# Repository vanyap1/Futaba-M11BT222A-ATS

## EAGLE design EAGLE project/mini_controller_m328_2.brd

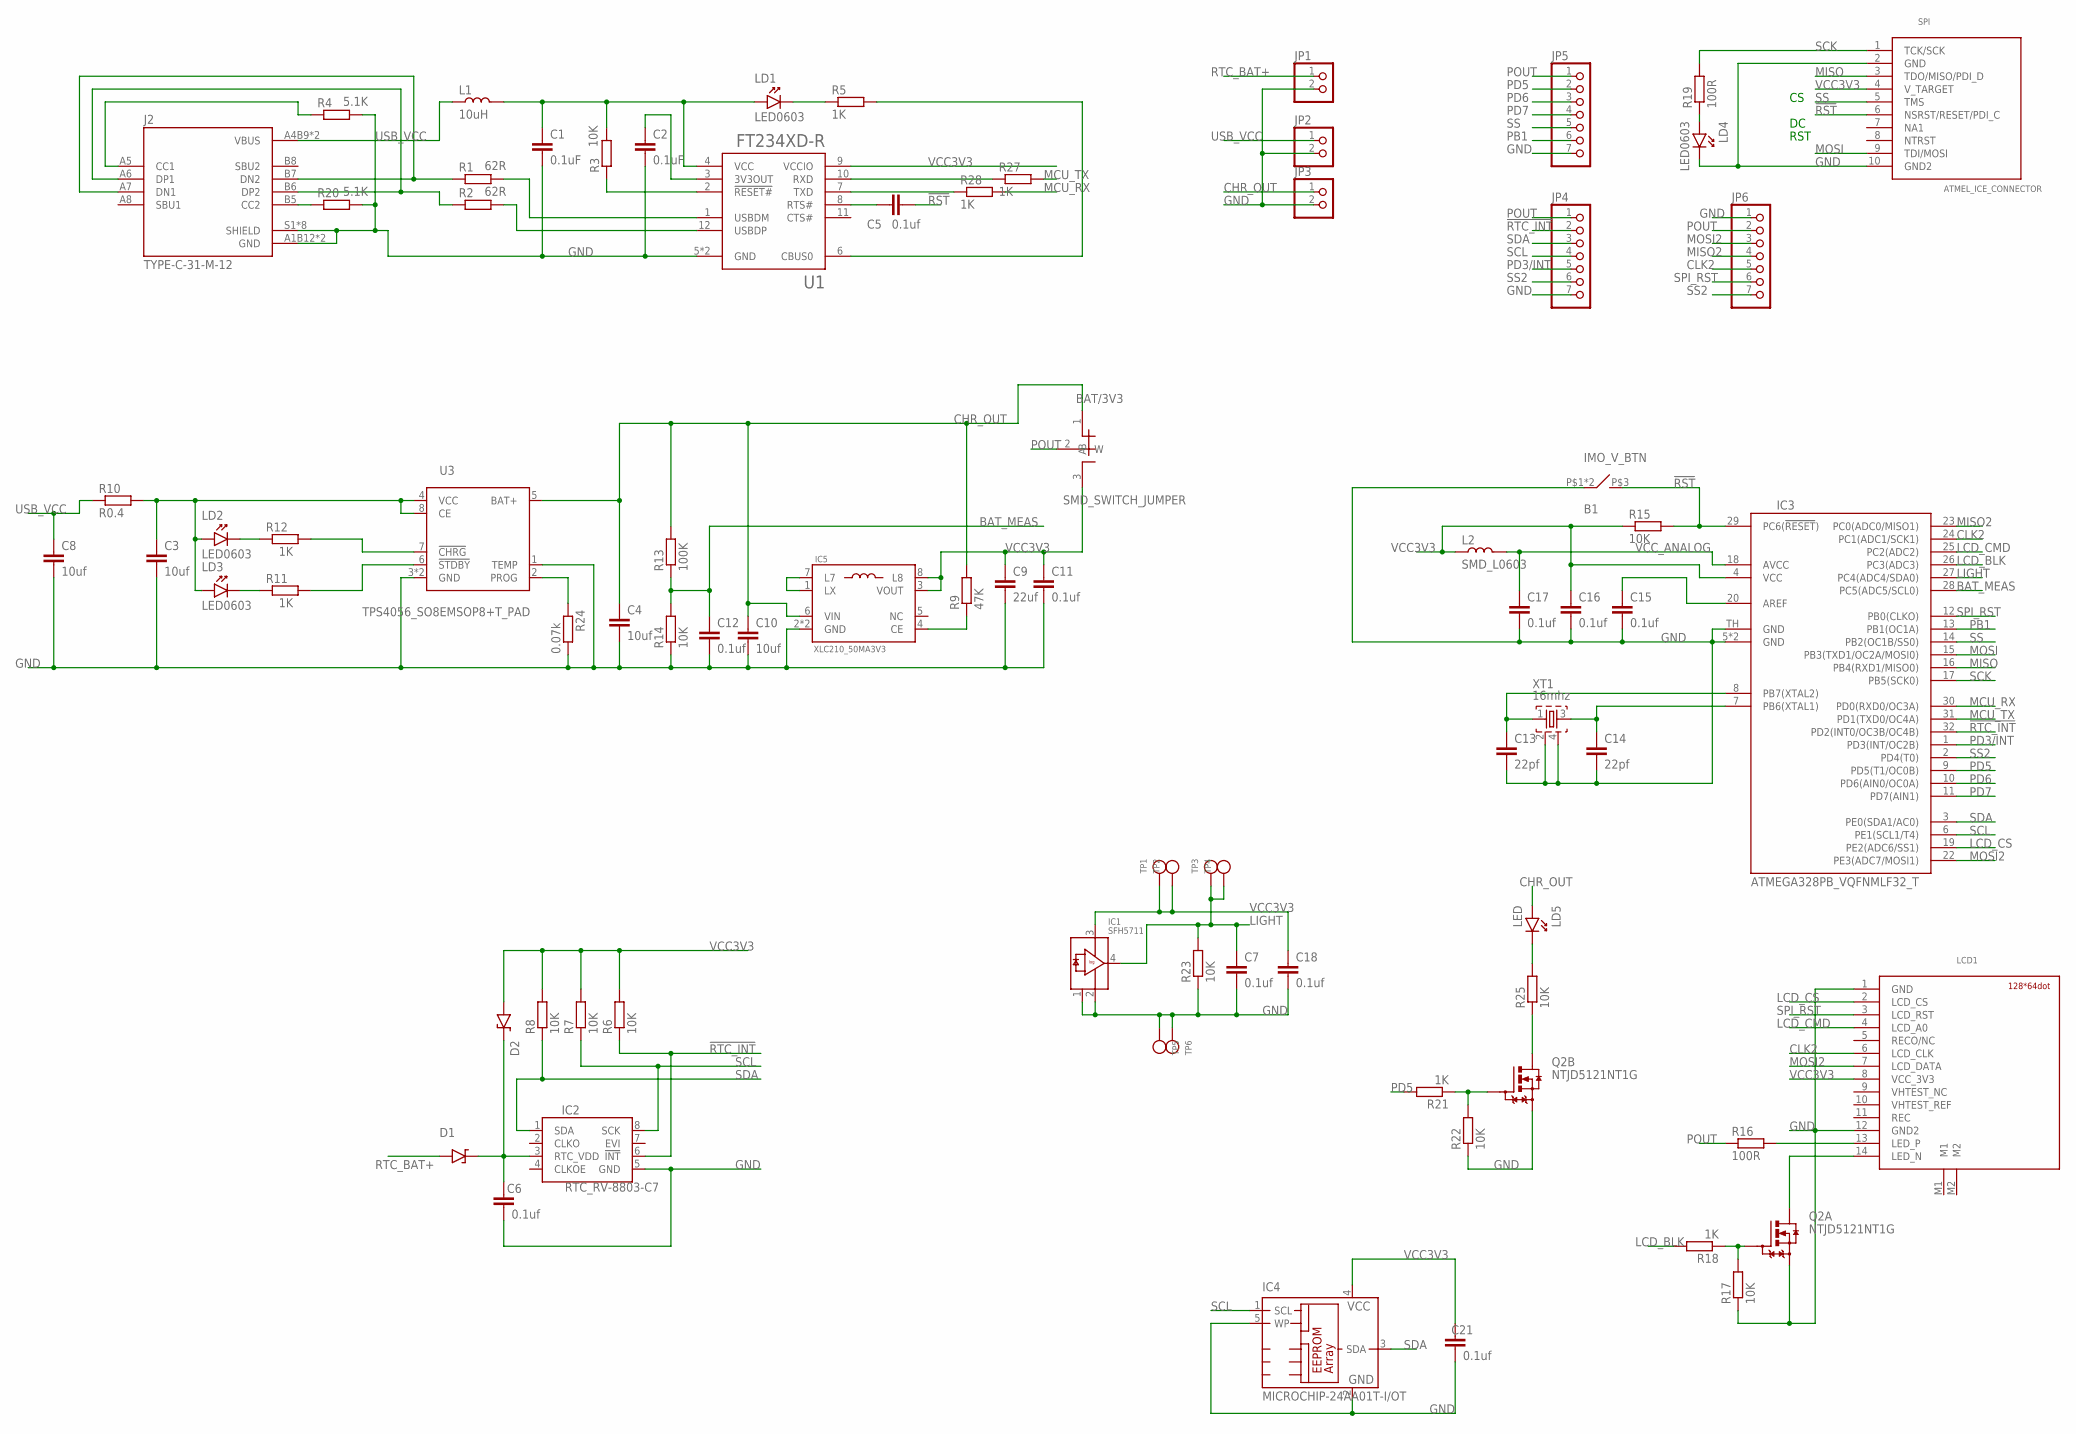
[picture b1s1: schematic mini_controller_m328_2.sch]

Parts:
B1: IMO_V_BTN; IMO_V_BNN
BAT/3V3: SMD_SWITCH_JUMPER; 0603_JUMP
C1, C2: 0.1uF; 0603
C3, C4, C8: 10uf; 1206
C5, C6, C7, C11, C12, C15, C16, C17, C18, C21: 0.1uf; 0603
C9: 22uf; 0805
C10: 10uf; 0603
C13, C14: 22pf; 0603
D1, D2: D_SOD323; SOD-323_D
IC1: SFH5711
IC2: RTC_RV-8803-C7; C7_RTC
IC3: ATMEGA328PB_VQFNMLF32_T; MLF32-TH
IC4: MICROCHIP-24AA01T-I/OT; SOT-23(5)
IC5: XLC210_50MA3V3; XCL210_50MA3V3
J2: TYPE-C-31-M-12; HRO_TYPE-C-31-M-12
JP1, JP2, JP3: PINHD-1X2; 1X02
JP4, JP5, JP6: PINHD-1X7; 1X07
L1: 10uH; 0603
L2: SMD_L0603; 0603
LCD1: ALE_LCD_128X64; ALE_LCD_14PIN_CONNECTOR
LD1, LD2, LD3, LD4: LED0603; 0603_P
LD5: LED; 3MM_DIP_LED
Q2: NTJD5121NT1G; SOT363
R1, R2: 62R; 0603
R3, R6, R7, R8, R14, R15, R17, R22, R23, R25: 10K; 0603
R4, R20: 5.1K; 0603
R5, R11, R12, R18, R21, R27, R28: 1K; 0603
R9: 47K; 0603
R10: R0.4; 1206
R13: 100K; 0603
R16, R19: 100R; 0603
R24: 0.07k; 0603
SPI: ATMEL_ICE_CONNECTOR; MINI10P_SPI/JTAG/PDI
TP1, TP2, TP3, TP4, TP5, TP6: TEST_POINT_D2MM; TP
U1: FT234XD-R; IC_FT234XD-R
U3: TPS4056_SO8EMSOP8+T_PAD; EMSOP8+TPAD
XT1: 16mhz; QUARTZ_3X3MM

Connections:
!RST: B1.P$3 (4), C5.2, IC3.29 (PC6(!RESET!)), R15.2, SPI.6 (NSRST/RESET/PDI_C)
!RTC_INT: IC2.6 (!INT), IC3.32 (PD2(INT0/OC3B/OC4B)), JP4.2, R6.1
BAT_MEAS: C12.1, IC3.28 (PC5(ADC5/SCL0)), R13.1, R14.2
CHR_OUT: BAT/3V3.1 (A), C4.1, C10.1, IC5.6 (VIN), JP3.1, LD5.A, R9.2, R13.2, U3.5 (BAT+)
CLK2: IC3.24 (PC1(ADC1/SCK1)), JP6.5, LCD1.6 (LCD_CLK)
DM2: R1.2, U1.1 (USBDM)
DP2: R2.2, U1.12 (USBDP)
GND: B1.P$1 (1), B1.P$2 (1), C1.2, C2.2, C3.2, C4.2, C6.2, C7.2, C8.2, C9.2, C10.2, C11.2, C12.2, C13.2, C14.2, C15.2, C16.2, C17.2, C18.2, C21.2, IC1.1, IC1.2, IC2.5 (GND), IC3.5 (GND), IC3.21 (GND), IC3.TH (GND), IC4.2 (GND), IC4.5 (WP), IC5.2 (GND), IC5.9 (GND), J2.A1B12 (GND), J2.B1A12 (GND), J2.S1 (SHIELD), J2.S2 (SHIELD), J2.S3 (SHIELD), J2.S4 (SHIELD), J2.S5 (SHIELD), J2.S6 (SHIELD), J2.S7 (SHIELD), J2.S8 (SHIELD), JP1.2, JP2.2, JP3.2, JP4.7, JP5.7, JP6.1, LCD1.1 (GND), LCD1.12 (GND2), LD4.1 (K), Q2.1 (S), Q2.4 (S), R4.2, R14.1, R17.1, R20.2, R22.1, R23.1, R24.2, SPI.2 (GND), SPI.10 (GND2), TP5.P$1, TP6.P$1, U1.5 (GND), U1.13 (GND), U3.1 (TEMP), U3.3 (GND), U3.TPAD (GND), XT1.2, XT1.4
LCD_BLK: IC3.26 (PC3(ADC3)), R18.2
LCD_CMD: IC3.25 (PC2(ADC2)), LCD1.4 (LCD_A0)
LCD_CS: IC3.19 (PE2(ADC6/SS1)), LCD1.2 (LCD_CS)
LIGHT: C7.1, IC1.4, IC3.27 (PC4(ADC4/SDA0)), R23.2, TP3.P$1, TP4.P$1
MCU_RX: IC3.30 (PD0(RXD0/OC3A)), R28.2
MCU_TX: IC3.31 (PD1(TXD0/OC4A)), R27.2
MISO: IC3.16 (PB4(RXD1/MISO0)), SPI.3 (TDO/MISO/PDI_D)
MISO2: IC3.23 (PC0(ADC0/MISO1)), JP6.4
MOSI: IC3.15 (PB3(TXD1/OC2A/MOSI0)), SPI.9 (TDI/MOSI)
MOSI2: IC3.22 (PE3(ADC7/MOSI1)), JP6.3, LCD1.7 (LCD_DATA)
unnamed: LCD1.13 (LED_P), R16.2
unnamed: LCD1.14 (LED_N), Q2.6 (D)
unnamed: IC5.1 (LX), IC5.7 (L7)
unnamed: Q2.2 (G), R17.2, R18.1
unnamed: IC5.4 (CE), R9.1
unnamed: C3.1, LD2.2 (A), LD3.2 (A), R10.2, U3.4 (VCC), U3.8 (CE)
unnamed: C1.1, L1.2, LD1.2 (A), R3.2, U1.4 (VCC)
unnamed: C13.1, IC3.8 (PB7(XTAL2)), XT1.1
unnamed: C2.1, U1.3 (3V3OUT)
unnamed: LD1.1 (K), R5.1
unnamed: R5.2, U1.6 (CBUS0)
unnamed: C14.1, IC3.7 (PB6(XTAL1)), XT1.3
unnamed: R24.1, U3.2 (PROG)
unnamed: R27.1, U1.10 (RXD)
unnamed: C5.1, U1.8 (RTS#)
unnamed: LD4.2 (A), R19.1
unnamed: J2.A5 (CC1), R4.1
unnamed: R12.2, U3.7 (!CHRG)
unnamed: C6.1, D1.K, D2.K, IC2.3 (RTC_VDD)
unnamed: C15.1, IC3.20 (AREF)
unnamed: J2.A7 (DN1), J2.B7 (DN2), R1.1
unnamed: J2.A6 (DP1), J2.B6 (DP2), R2.1
unnamed: LD2.1 (K), R12.1
unnamed: LD3.1 (K), R11.1
unnamed: R11.2, U3.6 (!STDBY)
unnamed: Q2.5 (G), R21.1, R22.2
unnamed: R28.1, U1.7 (TXD)
unnamed: J2.B5 (CC2), R20.1
unnamed: LD5.K, R25.2
unnamed: Q2.3 (D), R25.1
PB1: IC3.13 (PB1(OC1A)), JP5.6
PD3/INT: IC3.1 (PD3(INT/OC2B)), JP4.5
PD5: IC3.9 (PD5(T1/OC0B)), JP5.2, R21.2
PD6: IC3.10 (PD6(AIN0/OC0A)), JP5.3
PD7: IC3.11 (PD7(AIN1)), JP5.4
POUT: BAT/3V3.2 (W), JP4.1, JP5.1, JP6.2, R16.1
RTC_BAT+: D1.A, JP1.1
SCK: IC3.17 (PB5(SCK0)), R19.2, SPI.1 (TCK/SCK)
SCL: IC2.8 (SCK), IC3.6 (PE1(SCL1/T4)), IC4.1 (SCL), JP4.4, R7.1
SDA: IC2.1 (SDA), IC3.3 (PE0(SDA1/AC0)), IC4.3 (SDA), JP4.3, R8.1
SER_RST: R3.1, U1.2 (!RESET#)
SPI_RST: IC3.12 (PB0(CLKO)), JP6.6, LCD1.3 (LCD_RST)
SS: IC3.14 (PB2(OC1B/SS0)), JP5.5, SPI.5 (TMS)
SS2: IC3.2 (PD4(T0)), JP4.6, JP6.7
USB_VCC: C8.1, J2.A4B9 (VBUS), J2.B4A9 (VBUS), JP2.1, L1.1, R10.1
VCC3V3: BAT/3V3.3 (B), C9.1, C11.1, C16.1, C18.1, C21.1, D2.A, IC1.3, IC3.4 (VCC), IC4.4 (VCC), IC5.3 (VOUT), IC5.8 (L8), L2.1, LCD1.8 (VCC_3V3), R6.2, R7.2, R8.2, R15.1, SPI.4 (V_TARGET), TP1.P$1, TP2.P$1, U1.9 (VCCIO)
VCC_ANALOG: C17.1, IC3.18 (AVCC), L2.2

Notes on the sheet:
RST

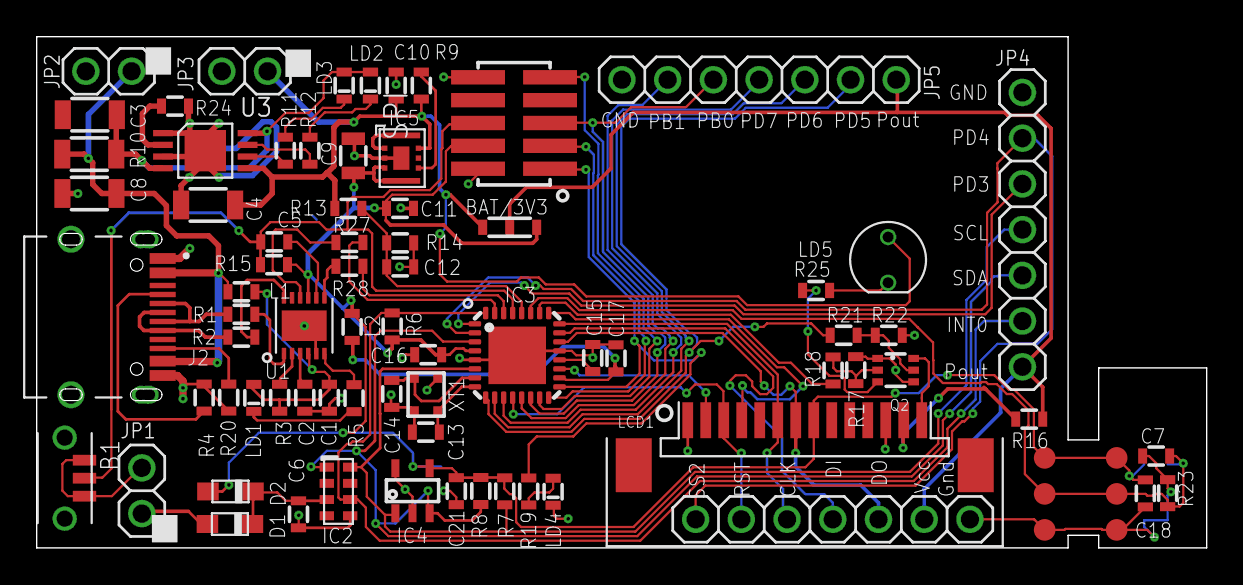
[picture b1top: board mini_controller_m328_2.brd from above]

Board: 2 copper layers, 65.0 x 28.4 mm, 81 parts (1 on the bottom side), 65 nets.

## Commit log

2023-11-07 New project created
2023-11-21 now its working setup
2023-11-23 added RTC driver
2023-12-03 added i2c light sensor {ISL29034} and disc pictogram fix
